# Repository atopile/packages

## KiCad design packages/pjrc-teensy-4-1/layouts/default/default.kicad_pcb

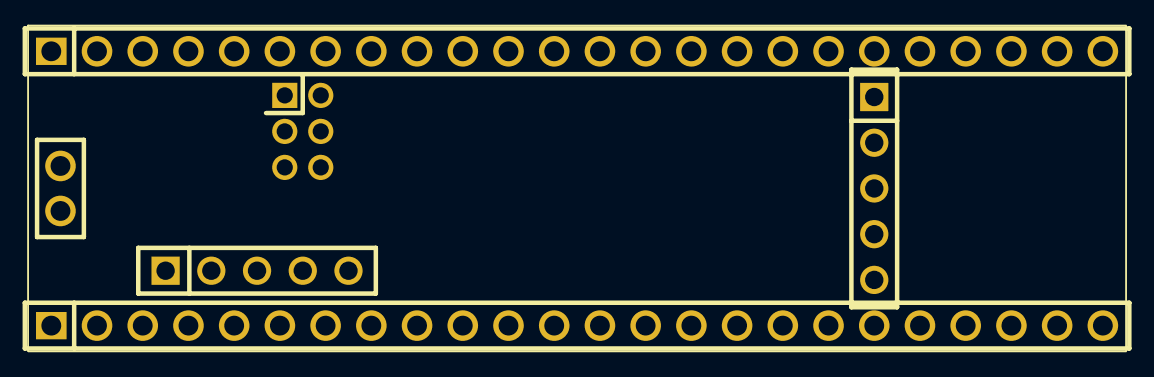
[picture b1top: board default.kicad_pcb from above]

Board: 2 copper layers, 7 parts (0 on the bottom side), 2 nets, no tracks yet.

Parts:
CN1: CONN-TH_2P-P2.50_YZ88715155P-02025-01
U1, U2: HDR-TH_24P-P2.54-V-F
U3: PJRC_Teensy_4_1
U4, U5: HDR-TH_5P-P2.54-V-F
U6: HDR-TH_6P-P2.00-V-F-R2-C3-S2.00

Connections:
hv: U1.15, U2.3, U4.4
lv: U1.1, U2.2, U2.15, U4.3, U5.4, U5.5

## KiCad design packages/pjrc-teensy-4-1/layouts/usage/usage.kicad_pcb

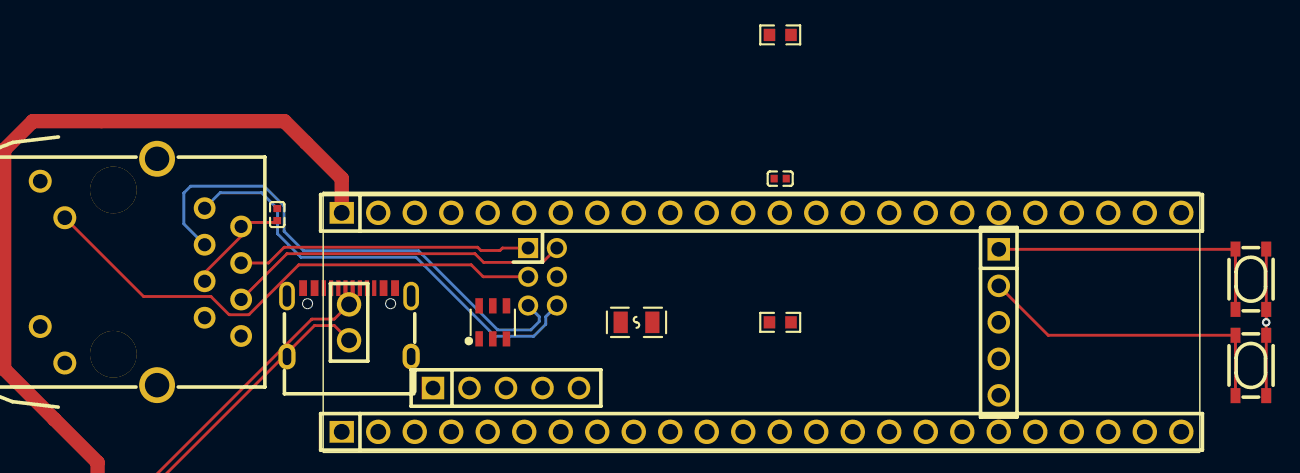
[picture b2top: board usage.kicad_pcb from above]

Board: 2 copper layers, 17 parts (0 on the bottom side), 17 nets.

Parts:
C1, C2: 0F; C0402
CN1: CONN-TH_2P-P2.50_YZ88715155P-02025-01
D1: SOT-23-6_L2.9-W1.6-P0.95-LS2.8-BL
F1: F0805
R1, R2: 10000Ω; R0603
RJ1: RJ45-TH_J1B1211CCD
SW1, SW2: KEY-SMD_4P-L4.2-W3.2-P2.20-LS4.6
U1: HDR-TH_6P-P2.00-V-F-R2-C3-S2.00
U2, U5: HDR-TH_5P-P2.54-V-F
U3, U4: HDR-TH_24P-P2.54-V-F
U6: PJRC_Teensy_4_1
USB1: USB-C-SMD_TYPE-C-6PIN-2MD-073

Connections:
10: R2.1, USB1.10
ETH_LED_SPEED: RJ1.10, U1.3
ETH_RX_N: RJ1.6, U1.2
ETH_RX_P: RJ1.4, U1.1
ETH_TX_N: RJ1.3, U1.5
ETH_TX_P: RJ1.1, U1.6
USB_N: CN1.1, D1.1, D1.6, USB1.5, USB1.7
USB_P: CN1.2, D1.3, D1.4, USB1.6, USB1.8
cc[0]-4: R1.1, USB1.4
hv: C1.1, RJ1.8, RJ1.9, RJ1.13, RJ1.14, U1.4
input: SW1.1, SW1.2, U2.1
lv: C1.2, RJ1.2, RJ1.5
power_3v3-hv: U2.4, U3.15, U4.3
power_usb_host-lv: C2.2, D1.2, R1.2, R2.2, SW1.3, SW1.4, SW2.3, SW2.4, U2.3, U3.1, U4.2, U4.15, U5.4, U5.5, USB1.1, USB1.12, USB1.13, USB1.14, USB1.15, USB1.16
power_vbus-hv: F1.1, USB1.2, USB1.11
program-input: SW2.1, SW2.2, U2.2
teensy-power-hv: C2.1, D1.5, F1.2, U4.1
